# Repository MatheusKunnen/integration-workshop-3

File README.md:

# Snacks Control System

This project was created for the Integration Workshop 3 within the Computer Engineering curriculum during the second semester of 2023 at UTFPR University.

**Team Members**

- Alessandra Fernandes Lacerda
- Gabriel Henrique Linke
- Ivan Bauer Jr.
- Matheus Kunnen Ledesma _(Project Manager)_
- Meika Farias de Oliveira
- Patricia Abe Turato

**Orientators**

- Prof. Dr. Heitor Silvério Lopes
- Prof. Dr. João Alberto Fabro

## Overview

A frequent concern of parents is the difficulty in controlling their children's eating habits at school, as children need healthy snacks to support their growth and development. Unfortunately, many of the snacks provided in the school canteen are high in fat, sugar and salt. Furthermore, it is difficult to guarantee that children diagnosed with food allergies or intolerance do not eat foods containing ingredients that may cause a reaction. On top of that, kids might not know how to manage their money well and end up spending too much.

The project tries to solve these problems with a system that allows parents to manage the options of snacks shown to their kids, and a vending machine to distribute these snacks.

The mobile application allows parents to register their children in the system, select the specific snacks that will be available for them to buy and specify their daily budget. The vending machine identifies the child and shows all available authorized food options along with the available budget. Finally, when the desired product is selected, the machine asks for confirmation and then delivers the snack.

## Acknowledgements

The team would like to express their deepest gratitude to Professor Dr. Heitor Silvério Lopes and Professor Dr. João Alberto Fabro for their guidance and support during the development of the project. Also, the team is thankful to all the professors of Computer Engineering at UTFPR for their contributions to the team members academic growth. Their collective efforts in imparting knowledge and sharing experiences were fundamental to the development of capabilities that made this a successful project.

## Useful links

- Blog: https://alelacerda.notion.site/Snacks-Control-System-76155e9a51a641b1811bb6345904a688?pvs=4
- Video: https://youtu.be/sgXLWZ9KaMk

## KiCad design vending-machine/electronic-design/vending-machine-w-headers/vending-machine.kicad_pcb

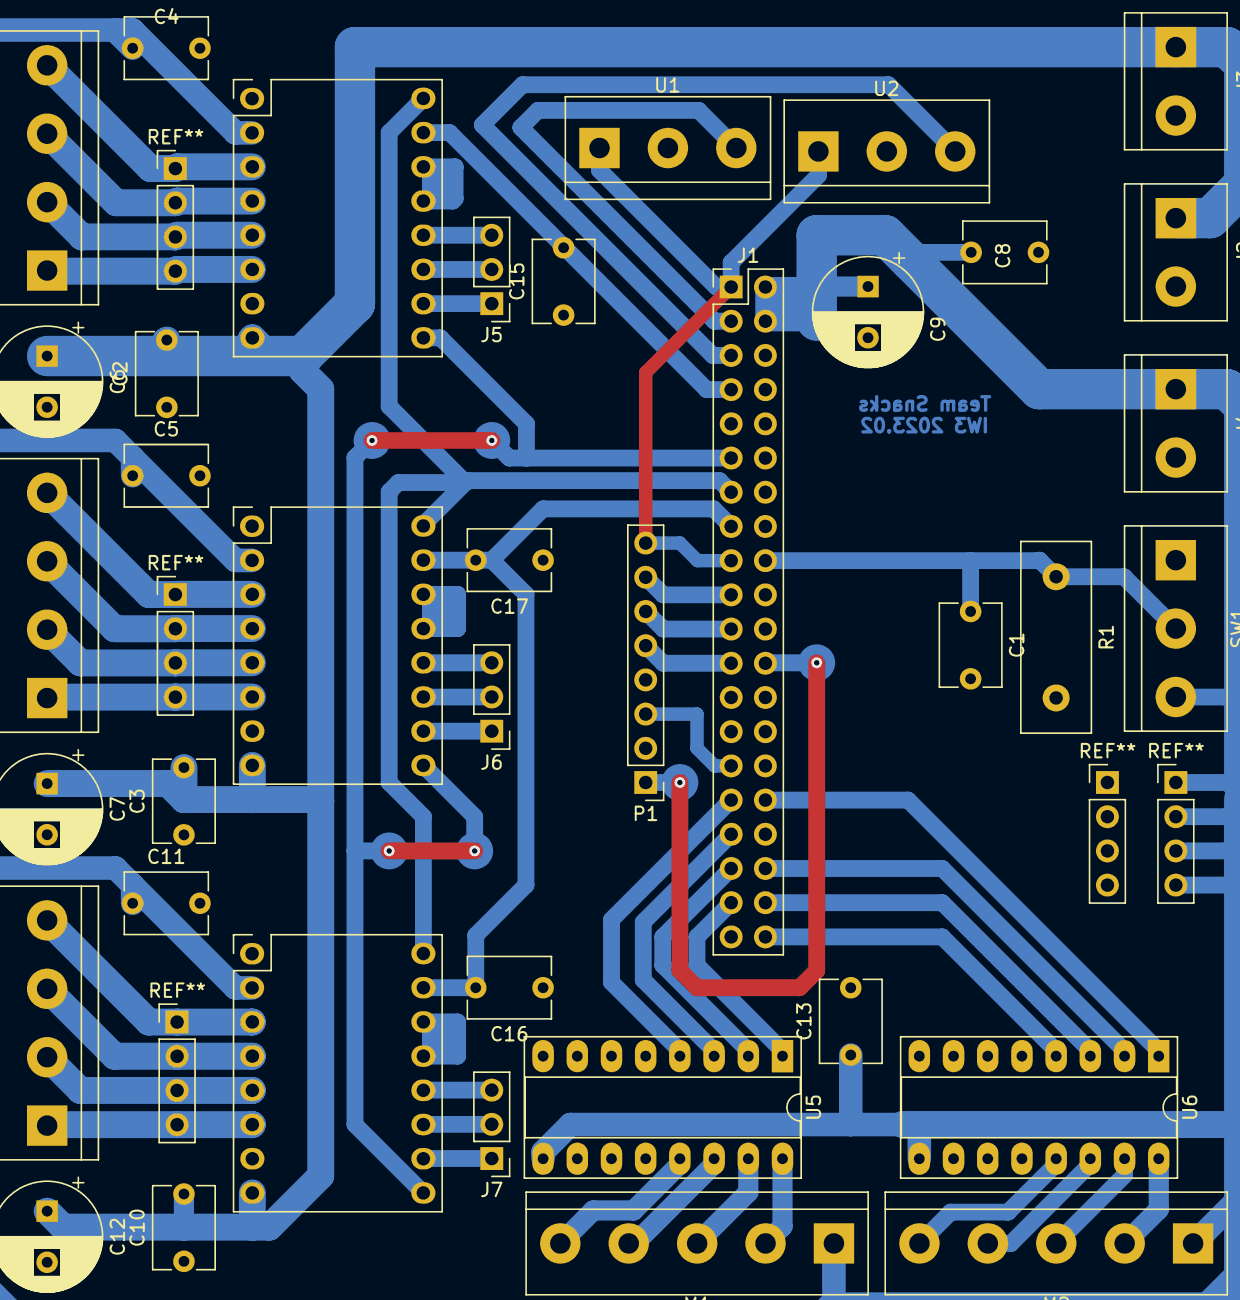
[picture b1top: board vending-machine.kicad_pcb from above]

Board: 2 copper layers, 38 parts (0 on the bottom side), 56 nets.

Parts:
C1, C2, C3, C4, C5, C8, C10, C11, C13: 100nF; C_Disc_D6.0mm_W4.4mm_P5.00mm
C6, C7, C9, C12: 220uF; CP_Radial_D8.0mm_P3.80mm
C15, C16, C17: 100n; C_Disc_D6.0mm_W4.4mm_P5.00mm
J1: Raspberry_Pi_4; PinHeader_2x20_P2.54mm_Vertical
J2: 12V Input; TerminalBlock_bornier-2_P5.08mm
J3: 12V Output; TerminalBlock_bornier-2_P5.08mm
J4: 5V Input; TerminalBlock_bornier-2_P5.08mm
J5, J6, J7: Conn_01x03_Male; PinHeader_1x03_P2.54mm_Vertical
J8, J9, J10: Motor; TerminalBlock_bornier-4_P5.08mm
M1, M2: Stepper_Motor_unipolar_5pin; TerminalBlock_bornier-5_P5.08mm
P1: RFID-RC522-MODULE; PinHeader_1x08_P2.54mm_Vertical
R1: 10K; R_Box_L14.0mm_W5.0mm_P9.00mm
SW1: SW_SPDT; TerminalBlock_bornier-3_P5.08mm
U1, U2: IR-D; TerminalBlock_bornier-3_P5.08mm
U3, U4, U7: A4988; Pololu_A4988
U5, U6: ULN2003A; DIP-16_W7.62mm_Socket_LongPads

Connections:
+3V3: J1.1 (3V3), J1.17 (3V3), P1.8 (3.3V), U1.1 (VCC), U2.1 (VCC)
+5V: C4.1, C5.1, C8.2, C9.1, C11.1, C13.1, J1.2 (5V), J1.4 (5V), J4.1, M1.1, M2.1, SW1.3 (C), U3.2 (VDD), U4.2 (VDD), U5.9 (COM), U6.9 (COM), U7.2 (VDD)
+12V: C2.2, C3.2, C6.1, C7.1, C10.2, C12.1, J2.1, J3.1, U3.8 (VMOT), U4.8 (VMOT), U7.8 (VMOT)
D CNTRL I1: J1.32 (PWM0/GPIO12), U6.1 (I1)
D CNTRL I2: J1.36 (GPIO16), U6.2 (I2)
D CNTRL I3: J1.38 (GPIO20/MOSI1), U6.3 (I3)
D CNTRL I4: J1.40 (GPIO21/SCLK1), U6.4 (I4)
DIR CNTRL: J1.13 (GPIO27), U3.16 (DIR), U4.16 (DIR), U7.16 (DIR)
EN CNTRL: J1.11 (GPIO17), U3.9 (EN), U4.9 (EN), U7.9 (EN)
GND: C1.2, C2.1, C3.1, C4.2, C5.2, C6.2, C7.2, C8.1, C9.2, C10.1, C11.2, C12.2, C13.2, C15.1, C16.1, C17.1, J1.6 (GND), J1.9 (GND), J1.14 (GND), J1.20 (GND), J1.25 (GND), J1.30 (GND), J1.34 (GND), J1.39 (GND), J2.2, J3.2, J4.2, P1.4 (GND), R1.2, U1.2 (GND), U2.2 (GND), U3.1 (GND), U3.7 (GND), U4.1 (GND), U4.7 (GND), U5.8 (GND), U6.8 (GND), U7.1 (GND), U7.7 (GND)
H STEP CNTRL: C15.2, J1.7 (GCLK0/GPIO4), U3.15 (STEP)
H Sensor: J1.5 (SCL/GPIO3), U2.3 (SIG)
Limit SW: C1.1, J1.18 (GPIO24), R1.1, SW1.2 (B)
unnamed: J5.1, U3.10 (MS1)
unnamed: J5.2, U3.11 (MS2)
unnamed: J5.3, U3.12 (MS3)
unnamed: J6.1, U4.10 (MS1)
unnamed: J6.2, U4.11 (MS2)
unnamed: J6.3, U4.12 (MS3)
unnamed: J7.1, U7.10 (MS1)
unnamed: J7.2, U7.11 (MS2)
unnamed: J7.3, U7.12 (MS3)
unnamed: J8.1, U3.6 (2B)
unnamed: J8.2, U3.5 (2A)
unnamed: J8.3, U3.4 (1A)
unnamed: J8.4, U3.3 (IB)
unnamed: J9.1, U4.6 (2B)
unnamed: J9.2, U4.5 (2A)
unnamed: J9.3, U4.4 (1A)
unnamed: J9.4, U4.3 (IB)
unnamed: J10.1, U7.6 (2B)
unnamed: J10.2, U7.5 (2A)
unnamed: J10.3, U7.4 (1A)
unnamed: J10.4, U7.3 (IB)
unnamed: M1.2, U5.16 (O1)
unnamed: M1.3 (-), U5.15 (O2)
unnamed: M1.4, U5.14 (O3)
unnamed: M1.5, U5.13 (O4)
unnamed: M2.2, U6.16 (O1)
unnamed: M2.3 (-), U6.15 (O2)
unnamed: M2.4, U6.14 (O3)
unnamed: M2.5, U6.13 (O4)
unnamed: U3.13 (RST), U3.14 (SLP)
unnamed: U4.13 (RST), U4.14 (SLP)
unnamed: U7.13 (RST), U7.14 (SLP)
PD CNTRL I1: J1.37 (GPIO26), U5.1 (I1)
PD CNTRL I2: J1.35 (GPIO19/MISO1), U5.2 (I2)
PD CNTRL I3: J1.33 (PWM1/GPIO13), U5.3 (I3)
PD CNTRL I4: J1.31 (GCLK2/GPIO6), U5.4 (I4)
RFID MISO: J1.21 (MISO0/GPIO9), P1.6 (MISO)
RFID MOSI: J1.19 (MOSI0/GPIO10), P1.7 (MOSI)
RFID RST: J1.29 (GCLK1/GPIO5), P1.3 (RST)
RFID SCK: J1.23 (SCLK0/GPIO11), P1.5 (SCK)
RFID SDA: J1.24 (~CE0/GPIO8), P1.1 (SDA)
V STEP CNTRL: C16.2, C17.2, J1.15 (GPIO22), U4.15 (STEP), U7.15 (STEP)
V Sensor: J1.3 (SDA/GPIO2), U1.3 (SIG)

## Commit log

2023-09-21 Create docker and docker-compose for server
2023-09-22 Add use cases diagram
2023-09-24 Add activities diagrams
2023-09-25 Create react application base
2023-09-25 Create base react native project for mobile app
2023-09-26 Update diagrams
2023-09-27 Add first version of ER diagram
2023-09-27 Add first version of models and controllers
2023-10-01 Add architecture document
2023-10-01 Update folder structure to follow what was defined in the architecture doc
2023-10-03 Main board schematic
2023-10-03 Add motion system class diagram
2023-10-03 Add motion system architecture
2023-10-03 Add state diagram
2023-10-03 Update state diagram file name and update diagram
2023-10-03 Add auth middleware and login route for parent
2023-10-03 Create Login pages and service
2023-10-05 Schematic design
2023-10-05 Add child register and login endpoints
2023-10-08 Vending machine PDB final design
2023-10-09 Update routes
2023-10-09 Update PasswordGroup model and routes
2023-10-09 Update Children model and create route to get by tagNumber
2023-10-09 Update Snacks model and add get all options
2023-10-09 Add endpoint to get all parent's children
2023-10-09 Create route to update and delete child
2023-10-11 Adds icons and logo assets
2023-10-11 Adds custom colors
2023-10-11 Create custom button component
2023-10-11 Creates custom text input component
2023-10-11 Creates login screen
2023-10-11 Adds login screen to main app screen
2023-10-11 Adds home screen icons
2023-10-11 Creates child card component used on home screen
2023-10-11 Creates home screen
2023-10-12 Creates basic app navigation
2023-10-12 Alter global styles and button component
2023-10-12 Update login pages and add new routes
2023-10-12 Create order pages
2023-10-12 Create response pages
2023-10-13 Update children and image models
2023-10-13 Add new children endpoints
2023-10-14 Separate childSnackOrdersModel from childrenModel
2023-10-14 Add order history endpoint
2023-10-14 Create purchase endpoint
2023-10-14 Implement endpoint to get a random password group
2023-10-14 Add images and seeders
2023-10-14 Update some logic at the child controller
2023-10-14 Add auxiliar routes
2023-10-14 Update dockerfiles and readme
2023-10-14 Add Insomnia files with routes to test the API
2023-10-16 Adjusts purple color scheme
2023-10-16 Creates parent registration screen
2023-10-16 Creates manage child account and details screens
2023-10-17 Update seeder
2023-10-17 Update services, navigation and global styles
2023-10-18 Creates api access base
2023-10-18 Creates auth context for login information
2023-10-18 Creates login and parent register services
2023-10-19 Add endpoints to services, auth context and private routes
2023-10-19 Changes 'username' to 'e-mail' on ui
2023-10-19 Implements get children from parent service
2023-10-19 Implements details and account deletion service
2023-10-19 Sets status bar color to home screen
2023-10-23 Add swagger to the project
2023-10-24 Adds terms and conditions container
2023-10-24 Adjusts view when keyboard is showing
2023-10-24 Creates register child service
2023-10-24 Adds budget and snacks control screen
2023-10-24 Adds register child and budget and snacks to stack
2023-10-24 Add purchase snacks and get random password group to swagger
2023-10-24 Stepper drivers
2023-10-24 Sensors & switches reading
2023-10-24 Add Parents routes to swagger
2023-10-24 Update in design
2023-10-24 Alter ScrollView styles
2023-10-24 Add children routes to swagger
2023-10-24 Add auxiliar routes to swagger
2023-10-24 Adds terms and conditions
2023-10-26 Update page styles
2023-10-27 Base motion system project structure
2023-10-27 Rectify image login step
2023-10-27 Add socket server to the motion system
2023-10-28 Add cors middleware
2023-10-28 Add morgan middleware
2023-10-28 Change /snacks/purchase/:snack_id http method
2023-10-28 NFC reader implemented
2023-10-28 Fix module imports/exports
2023-10-28 Add ReflectanceSensor implementation
2023-10-28 Add limiter switch implementation
2023-10-29 Adds update snacks and budget services
2023-10-29 Add stepper drivers
2023-10-29 Add axis control
2023-10-29 Update WebSocketController and add websockets to web-app
2023-10-29 Updates server link
2023-10-29 Adds budget and snacks to register child flow
2023-10-30 Add compatibility with python < 3.10
2023-10-30 Add ProductDispenser class
2023-10-30 Improve axis calibration procedure
    Add move_to_pos method
2023-10-30 Add MotionSystemController base implementation
2023-10-30 Add Manual mode to motion system control
2023-10-30 Bug fix in stepper drivers
2023-10-31 Update velocities for ULN2009Driver
2023-10-31 Add logic to improve coupling
2023-10-31 Add slots default mapping
2023-10-31 Add product dispense to manual mode
2023-10-31 Remove testing code
2023-10-31 Adds order history screen and service
2023-11-01 Adds total spent to home screen
2023-11-01 Add websocket communication to order processing page
2023-11-01 NFCReader comm migrated to process + queue
2023-11-01 Add debug messages in WebSocketController
2023-11-01 Disable callback in LimiterSwitch & ReflectanceSensor
2023-11-01 Debug code removed
2023-11-01 Add flag to wait for NFC tag
2023-11-01 Add request product to motion system
2023-11-02 Fix bug in NFCReader
2023-11-02 Fix bug in processing order screen
2023-11-06 Reflectance sensor implemented
2023-11-06 Rectify treatment for credit available
2023-11-07 Add spinning icon to order processing page
2023-11-07 Add timeout for pages
2023-11-07 Fix display of snacks out of stock
2023-11-07 Add custom error messages
2023-11-07 Load products position from file
2023-11-07 Add home axis in move to position zero
2023-11-07 Improve product dispenser
2023-11-07 Disable manual mode menu
2023-11-07 Adds vertical padding on text input for ios
2023-11-07 Adds SafeAreaView to manage child account
2023-11-07 Adds border radius on budget control for ios
2023-11-07 Locks screen orientation
2023-11-07 Fixes order history not rendering properly
2023-11-07 Adds parent balance to home screen
2023-11-07 Fixes useEffect on Home screen
2023-11-10 Updates icon images to svg format
2023-11-10 Removes unnecessary console logs
2023-11-10 Adds option to logout from home screen
2023-11-10 Updates app icon
2023-11-10 Removes development team on iOS
2023-11-11 Update default slots positions
2023-11-11 Disable motors after steps ULN2003Driver
2023-11-11 Fix typo in ULN2009Driver
2023-11-11 Update product dispenser speed
2023-11-11 Add Process to stepper drivers
2023-11-11 Add exclusive process to MotionSystemController
2023-11-11 Set NFCReader process as daemon
2023-11-11 Avoid home if there's another request
2023-11-12 Add Motion System Monitor
2023-11-13 Fixes order history not showing properly
2023-11-13 Remove console logs
2023-11-20 Update vending machine firmware class diagram
2023-11-23 Improve reliability
2023-11-23 Update default parent balance value
